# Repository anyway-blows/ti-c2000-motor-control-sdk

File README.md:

# ti-c2000-motor-control-sdk
ti-c2000-motor-control-sdk

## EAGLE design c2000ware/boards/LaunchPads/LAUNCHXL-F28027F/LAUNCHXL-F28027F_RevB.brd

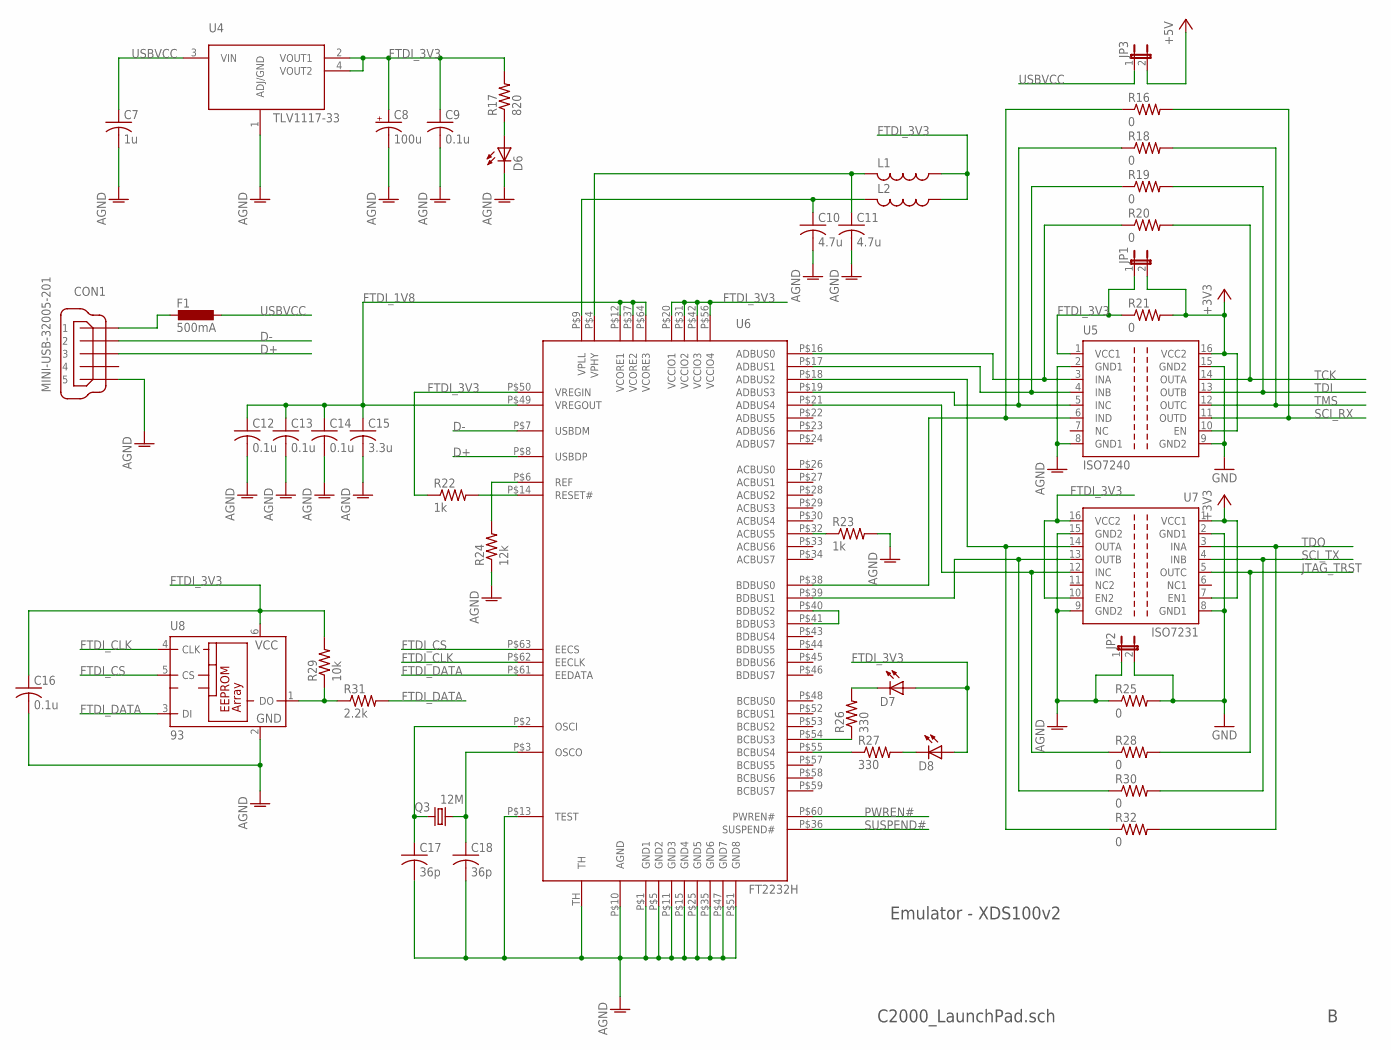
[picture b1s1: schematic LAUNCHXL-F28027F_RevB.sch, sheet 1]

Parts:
C7: 1u; C0402
C8: 100u; B/3528-21R
C9, C12, C13, C14, C16: 0.1u; C0402
C10, C11: 4.7u; C0402
C15: 3.3u; C0402
C17, C18: 36p; C0402
CON1: MINI-USB-32005-201; 32005-201
D6, D7, D8: LEDCHIP-LED0603; CHIP-LED0603
F1: 500mA; L1812
JP1, JP2, JP3: JP1ENORM; JP1
L1, L2: L-US0402; R0402
Q3: 12M; HC49UP
R16, R18, R19, R20, R21, R25, R28, R30, R32: 0; R1206
R17: 820; R0402
R22, R23: 1k; R0402
R24: 12k; R0402
R26, R27: 330; R0402
R29: 10k; R0402
R31: 2.2k; R0402
U4: TLV1117-33; SOT223
U5: ISO7240; SO-16DW
U6: FT2232H; QFN64
U7: ISO7231; SO-16DW
U8: 93; SOT23-6

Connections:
+3V3: JP1.2, R21.2, U5.10 (EN), U5.16 (VCC2), U7.1 (VCC1), U7.7 (EN1); also elsewhere on the board
+5V: JP3.2; also elsewhere on the board
AGND: C7.2, C8.-, C9.2, C10.2, C11.2, C12.2, C13.2, C14.2, C15.2, C16.2, C17.2, C18.2, CON1.5, D6.C, JP2.1, R23.2, R24.1, R25.1, U4.1 (ADJ/GND), U5.2 (GND1), U5.8 (GND1), U6.P$1 (GND1), U6.P$5 (GND2), U6.P$10 (AGND), U6.P$11 (GND3), U6.P$13 (TEST), U6.P$15 (GND4), U6.P$25 (GND5), U6.P$35 (GND6), U6.P$47 (GND7), U6.P$51 (GND8), U6.TH, U7.9 (GND2), U7.15 (GND2), U8.2 (GND)
D+: CON1.3, U6.P$8 (USBDP)
D-: CON1.2, U6.P$7 (USBDM)
FTDI_1V8: C12.1, C13.1, C14.1, C15.1, U6.P$12 (VCORE1), U6.P$37 (VCORE2), U6.P$49 (VREGOUT), U6.P$64 (VCORE3)
FTDI_3V3: C8.+, C9.1, C16.1, D7.A, D8.A, JP1.1, L1.1, L2.1, R17.2, R21.1, R22.1, R29.2, U4.2 (VOUT1), U4.4 (VOUT2), U5.1 (VCC1), U6.P$20 (VCCIO1), U6.P$31 (VCCIO2), U6.P$42 (VCCIO3), U6.P$50 (VREGIN), U6.P$56 (VCCIO4), U7.10 (EN2), U7.16 (VCC2), U8.6 (VCC)
FTDI_CLK: U6.P$62 (EECLK), U8.4 (CLK)
FTDI_CS: U6.P$63 (EECS), U8.5 (CS)
FTDI_DATA: R31.2, U6.P$61 (EEDATA), U8.3 (DI)
GND: JP2.2, R25.2, U5.9 (GND2), U5.15 (GND2), U7.2 (GND1), U7.8 (GND1); also elsewhere on the board
JTAG_TRST: R28.2, U7.5 (OUTC); also elsewhere on the board
unnamed: R20.1, U5.3 (INA), U6.P$16 (ADBUS0)
unnamed: C17.1, Q3.1, U6.P$2 (OSCI)
unnamed: R19.1, U5.4 (INB), U6.P$17 (ADBUS1)
unnamed: R32.1, U6.P$18 (ADBUS2), U7.14 (OUTA)
unnamed: R18.1, U5.5 (INC), U6.P$19 (ADBUS3)
unnamed: C18.1, Q3.2, U6.P$3 (OSCO)
unnamed: R29.1, R31.1, U8.1 (DO)
unnamed: R28.1, U6.P$21 (ADBUS4), U7.12 (INC)
unnamed: R23.1, U6.P$32 (ACBUS5)
unnamed: U6.P$40 (BDBUS2), U6.P$41 (BDBUS3)
unnamed: R16.1, U5.6 (IND), U6.P$38 (BDBUS0)
unnamed: R24.2, U6.P$6 (REF)
unnamed: R26.1, U6.P$54 (BCBUS3)
unnamed: C11.1, L1.2, U6.P$4 (VPHY)
unnamed: R30.1, U6.P$39 (BDBUS1), U7.13 (OUTB)
unnamed: R27.1, U6.P$55 (BCBUS4)
unnamed: D7.C, R26.2
unnamed: D8.C, R27.2
unnamed: C10.1, L2.2, U6.P$9 (VPLL)
unnamed: D6.A, R17.1
unnamed: R22.2, U6.P$14 (RESET#)
PWREN#: U6.P$60 (PWREN#)
SCI_RX: R16.2, U5.11 (OUTD); also elsewhere on the board
SCI_TX: R30.2, U7.4 (INB); also elsewhere on the board
SUSPEND#: U6.P$36 (SUSPEND#)
TCK: R20.2, U5.14 (OUTA); also elsewhere on the board
TDI: R19.2, U5.13 (OUTB); also elsewhere on the board
TDO: R32.2, U7.3 (INA); also elsewhere on the board
TMS: R18.2, U5.12 (OUTC); also elsewhere on the board
USBVCC: C7.1, F1.1, JP3.1, U4.3 (VIN)
XUSB: CON1.1, F1.2

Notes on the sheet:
Emulator - XDS100v2
C2000_LaunchPad.sch

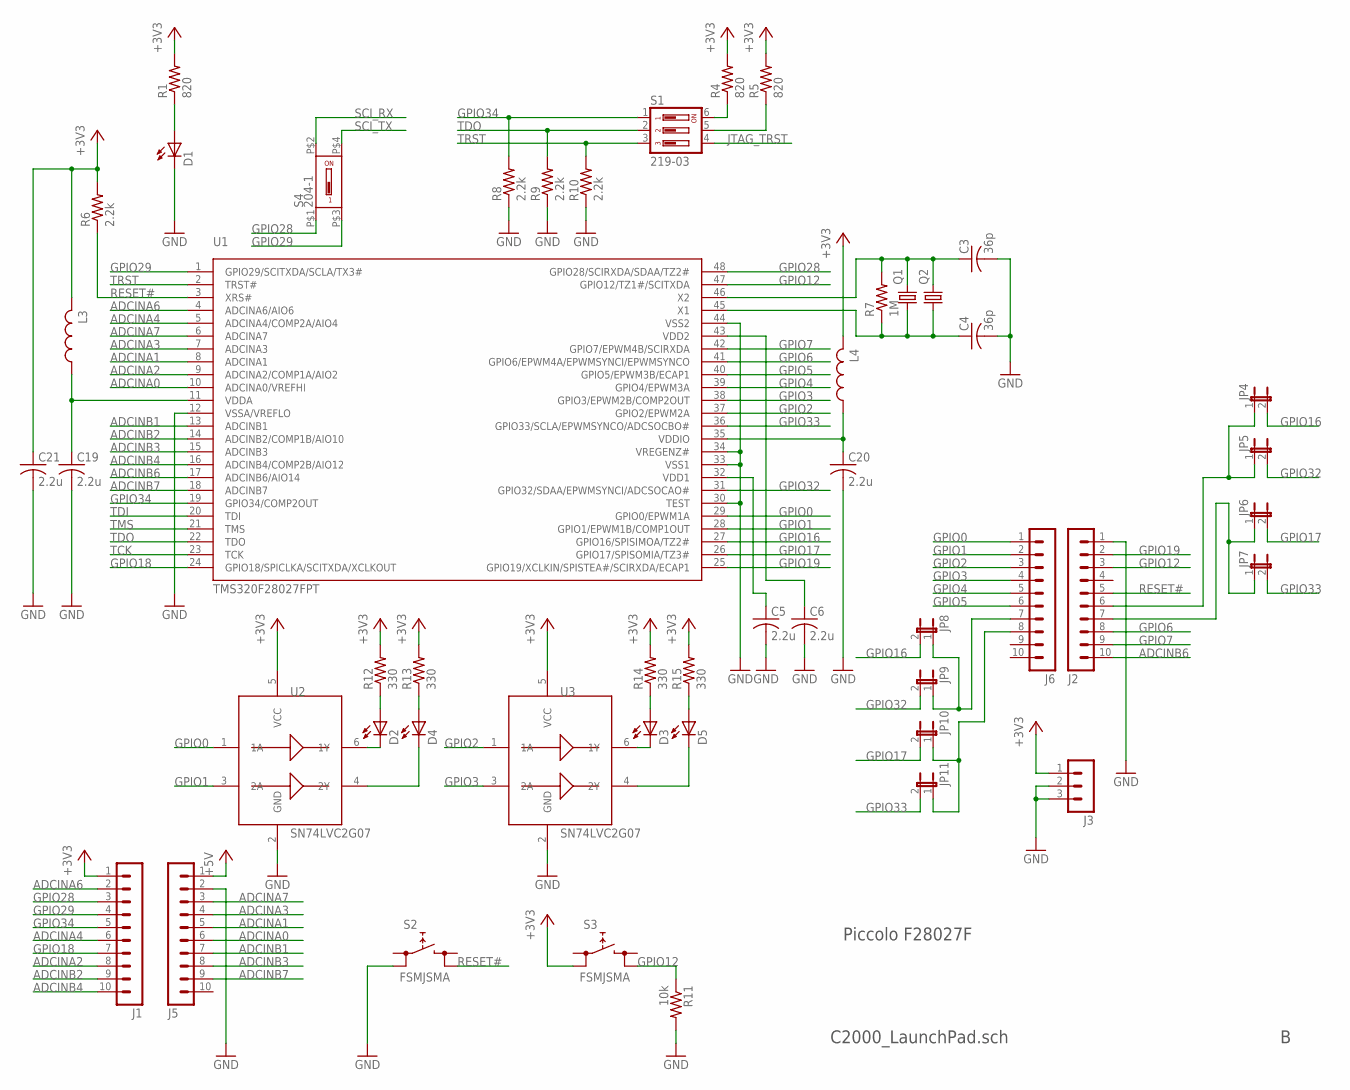
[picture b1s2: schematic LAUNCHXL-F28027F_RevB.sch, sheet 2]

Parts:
C3, C4: 36p; C0402
C5, C6, C19, C20, C21: 2.2u; C0402
D1, D2, D3, D4, D5: LEDCHIP-LED0603; CHIP-LED0603
J1, J2, J5, J6: MA10-1
J3: MA03-1
JP4, JP5, JP6, JP7, JP8, JP9, JP10, JP11: JP1ECUT; C0402
L3, L4: L-US0402; R0402
Q1: CRYSTALHC49S; HC49/S
Q2: CRYSTALHC49UP; HC49UP
R1, R4, R5: 820; R0402
R6, R8, R9, R10: 2.2k; R0402
R7: 1M; R0402
R11: 10k; R0402
R12, R13, R14, R15: 330; R0402
S1: 219-03; CTS-219-03
S2, S3: FSMJSMA
S4: 204-1; CTS-204-1
U1: TMS320F28027FPT; PQFP48
U2, U3: SN74LVC2G07; SOT23-6-DBV

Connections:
+3V3: C21.1, J1.1, J3.1, L3.2, L4.2, R1.2, R4.2, R5.2, R6.2, R12.2, R13.2, R14.2, R15.2, S3.P$2 (0), U2.5 (VCC), U3.5 (VCC); also elsewhere on the board
+5V: J5.1; also elsewhere on the board
ADCINA0: J5.6, U1.10 (ADCINA0/VREFHI)
ADCINA1: J5.5, U1.8 (ADCINA1)
ADCINA2: J1.8, U1.9 (ADCINA2/COMP1A/AIO2)
ADCINA3: J5.4, U1.7 (ADCINA3)
ADCINA4: J1.6, U1.5 (ADCINA4/COMP2A/AIO4)
ADCINA6: J1.2, U1.4 (ADCINA6/AIO6)
ADCINA7: J5.3, U1.6 (ADCINA7)
ADCINB1: J5.7, U1.13 (ADCINB1)
ADCINB2: J1.9, U1.14 (ADCINB2/COMP1B/AIO10)
ADCINB3: J5.8, U1.15 (ADCINB3)
ADCINB4: J1.10, U1.16 (ADCINB4/COMP2B/AIO12)
ADCINB6: J2.10, U1.17 (ADCINB6/AIO14)
ADCINB7: J5.9, U1.18 (ADCINB7)
GND: C3.2, C4.2, C5.2, C6.2, C19.2, C20.2, C21.2, D1.C, J2.1, J3.2, J3.3, J5.2, R8.1, R9.1, R10.1, R11.2, S2.P$2 (0), U1.12 (VSSA/VREFLO), U1.30 (TEST), U1.33 (VSS1), U1.34 (VREGENZ#), U1.44 (VSS2), U2.2 (GND), U3.2 (GND); also elsewhere on the board
GPIO0: J6.1, U1.29 (GPIO0/EPWM1A), U2.1 (1A)
GPIO1: J6.2, U1.28 (GPIO1/EPWM1B/COMP1OUT), U2.3 (2A)
GPIO2: J6.3, U1.37 (GPIO2/EPWM2A), U3.1 (1A)
GPIO3: J6.4, U1.38 (GPIO3/EPWM2B/COMP2OUT), U3.3 (2A)
GPIO4: J6.5, U1.39 (GPIO4/EPWM3A)
GPIO5: J6.6, U1.40 (GPIO5/EPWM3B/ECAP1)
GPIO6: J2.8, U1.41 (GPIO6/EPWM4A/EPWMSYNCI/EPWMSYNCO)
GPIO7: J2.9, U1.42 (GPIO7/EPWM4B/SCIRXDA)
GPIO12: J2.3, R11.1, S3.P$4 (1), U1.47 (GPIO12/TZ1#/SCITXDA)
GPIO16: JP4.2, JP8.2, U1.27 (GPIO16/SPISIMOA/TZ2#)
GPIO17: JP6.2, JP10.2, U1.26 (GPIO17/SPISOMIA/TZ3#)
GPIO18: J1.7, U1.24 (GPIO18/SPICLKA/SCITXDA/XCLKOUT)
GPIO19: J2.2, U1.25 (GPIO19/XCLKIN/SPISTEA#/SCIRXDA/ECAP1)
GPIO28: J1.3, S4.P$1 (1), U1.48 (GPIO28/SCIRXDA/SDAA/TZ2#)
GPIO29: J1.4, S4.P$3 (3), U1.1 (GPIO29/SCITXDA/SCLA/TX3#)
GPIO32: JP5.2, JP9.2, U1.31 (GPIO32/SDAA/EPWMSYNCI/ADCSOCAO#)
GPIO33: JP7.2, JP11.2, U1.36 (GPIO33/SCLA/EPWMSYNCO/ADCSOCBO#)
GPIO34: J1.5, R8.2, S1.1, U1.19 (GPIO34/COMP2OUT)
J2: J2.6, JP4.1, JP5.1
JTAG_TRST: S1.4; also elsewhere on the board
unnamed: C19.1, L3.1, U1.11 (VDDA)
unnamed: C3.1, Q1.2, Q2.2, R7.2, U1.46 (X2)
unnamed: R4.1, S1.6
unnamed: R5.1, S1.5
unnamed: C4.1, Q1.1, Q2.1, R7.1, U1.45 (X1)
unnamed: C5.1, U1.32 (VDD1)
unnamed: C6.1, U1.43 (VDD2)
unnamed: D1.A, R1.1
unnamed: D2.C, U2.6 (1Y)
unnamed: D4.C, U2.4 (2Y)
unnamed: D2.A, R12.1
unnamed: D4.A, R13.1
unnamed: D3.C, U3.6 (1Y)
unnamed: D5.C, U3.4 (2Y)
unnamed: D3.A, R14.1
unnamed: D5.A, R15.1
unnamed: C20.1, L4.1, U1.35 (VDDIO)
unnamed: J6.7, JP8.1, JP9.1
unnamed: J2.7, JP6.1, JP7.1
unnamed: J6.8, JP10.1, JP11.1
RESET#: J2.5, R6.1, S2.P$4 (1), U1.3 (XRS#)
SCI_RX: S4.P$2 (2); also elsewhere on the board
SCI_TX: S4.P$4 (4); also elsewhere on the board
TCK: U1.23 (TCK); also elsewhere on the board
TDI: U1.20 (TDI); also elsewhere on the board
TDO: R9.2, S1.2, U1.22 (TDO); also elsewhere on the board
TMS: U1.21 (TMS); also elsewhere on the board
TRST: R10.2, S1.3, U1.2 (TRST#)

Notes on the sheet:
Piccolo F28027F
C2000_LaunchPad.sch

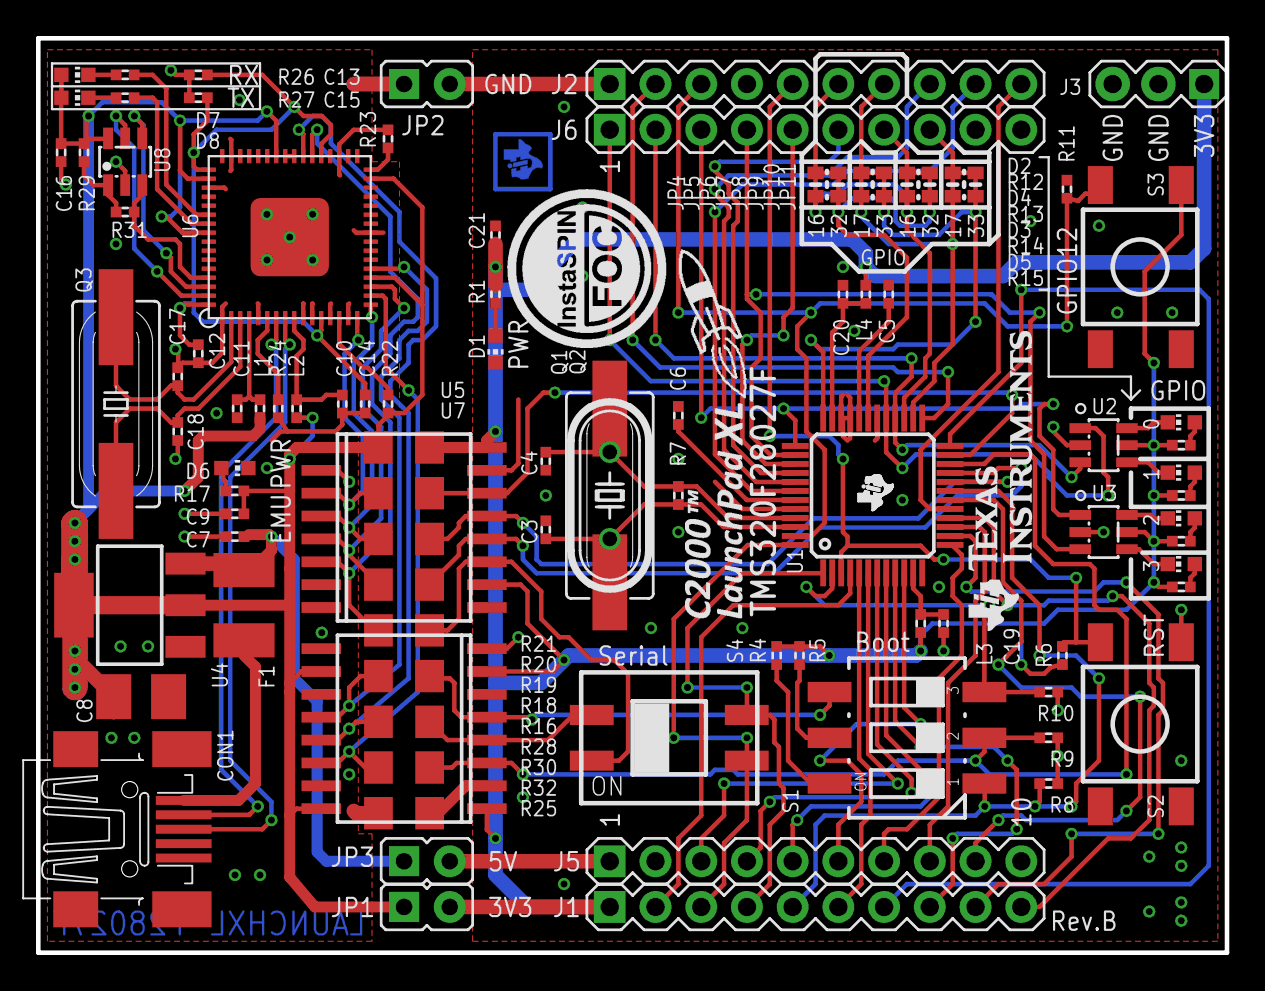
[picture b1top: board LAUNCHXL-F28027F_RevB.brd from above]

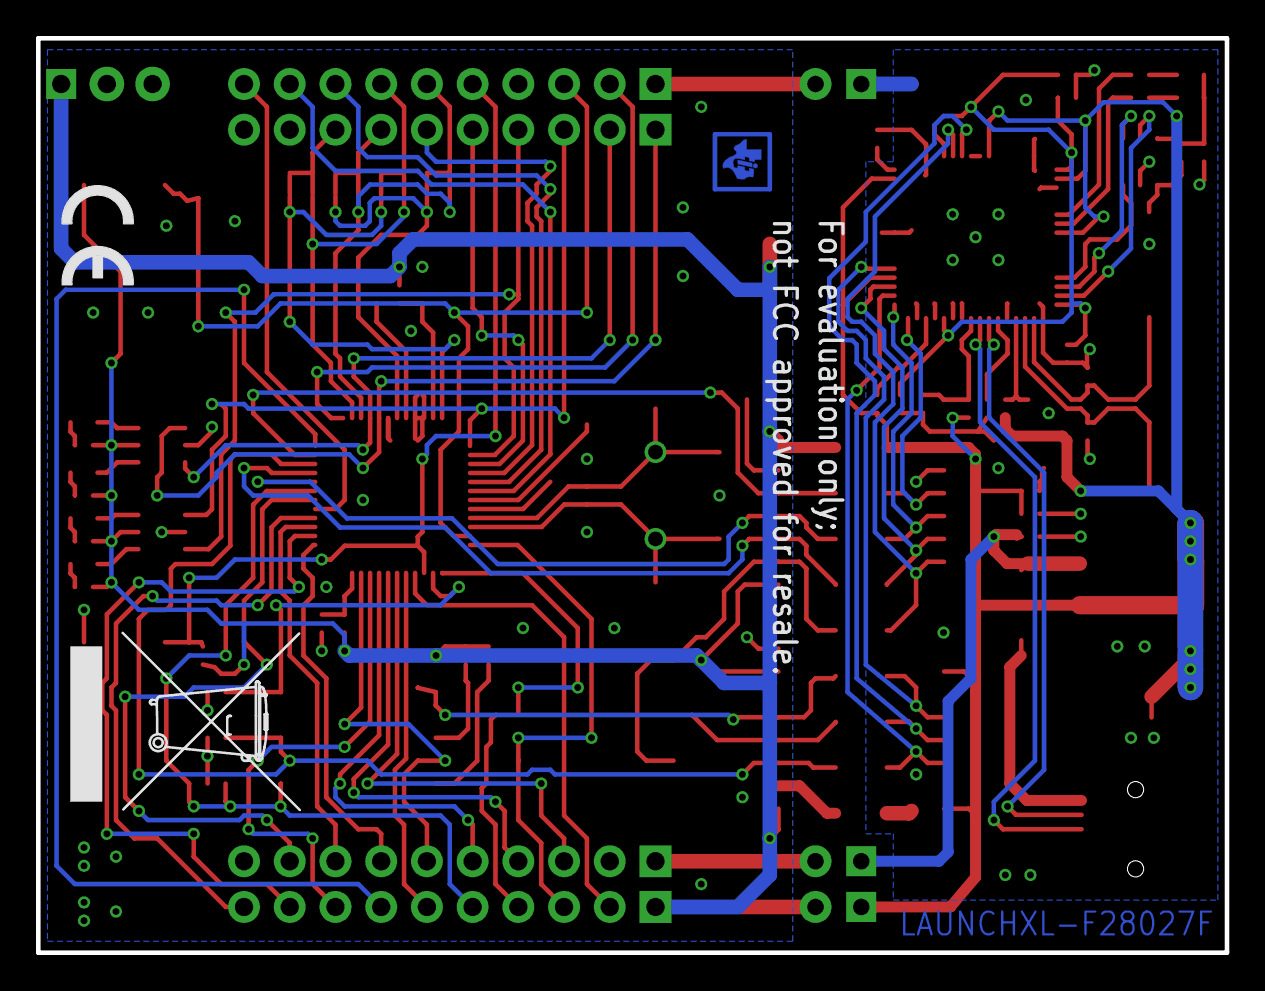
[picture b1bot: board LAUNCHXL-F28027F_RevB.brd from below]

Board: 2 copper layers, 66.0 x 50.8 mm, 103 parts (4 on the bottom side), 95 nets.

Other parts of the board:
U$1: TRADEMARK
U$2: XL
U$3: MSP430_LAB_TILOGO_SMALL
U$4: STI_LOGO_LOGO16_TPLACE
U$5: STI_LOGO_ROCKET
U$6: STI_LOGO_LAUNCHPADC2K
U$7: CE-4MM
U$8: MSP430_LAB_TILOGO_SMALL_TSTOP
U$11: TONNE_10.00

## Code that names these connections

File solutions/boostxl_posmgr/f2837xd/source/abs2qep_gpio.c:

//#############################################################################
//
// FILE:           abs2qep_gpio.c
//
// Description:    Example project for using pto_abs2qep Library.
//
//#############################################################################
// $TI Release: MotorControl SDK v3.03.00.00 $
// $Release Date: Tue Sep 21 16:33:28 CDT 2021 $
// $Copyright:
// Copyright (C) 2017-2021 Texas Instruments Incorporated - http://www.ti.com/
//
// Redistribution and use in source and binary forms, with or without
// modification, are permitted provided that the following conditions
// are met:
// 
//   Redistributions of source code must retain the above copyright
//   notice, this list of conditions and the following disclaimer.
// 
//   Redistributions in binary form must reproduce the above copyright
//   notice, this list of conditions and the following disclaimer in the
//   documentation and/or other materials provided with the
//   distribution.
// 
//   Neither the name of Texas Instruments Incorporated nor the names of
//   its contributors may be used to endorse or promote products derived
//   from this software without specific prior written permission.
// 
// THIS SOFTWARE IS PROVIDED BY THE COPYRIGHT HOLDERS AND CONTRIBUTORS
// "AS IS" AND ANY EXPRESS OR IMPLIED WARRANTIES, INCLUDING, BUT NOT
// LIMITED TO, THE IMPLIED WARRANTIES OF MERCHANTABILITY AND FITNESS FOR
// A PARTICULAR PURPOSE ARE DISCLAIMED. IN NO EVENT SHALL THE COPYRIGHT
// OWNER OR CONTRIBUTORS BE LIABLE FOR ANY DIRECT, INDIRECT, INCIDENTAL,
// SPECIAL, EXEMPLARY, OR CONSEQUENTIAL DAMAGES (INCLUDING, BUT NOT
// LIMITED TO, PROCUREMENT OF SUBSTITUTE GOODS OR SERVICES; LOSS OF USE,
// DATA, OR PROFITS; OR BUSINESS INTERRUPTION) HOWEVER CAUSED AND ON ANY
// THEORY OF LIABILITY, WHETHER IN CONTRACT, STRICT LIABILITY, OR TORT
// (INCLUDING NEGLIGENCE OR OTHERWISE) ARISING IN ANY WAY OUT OF THE USE
// OF THIS SOFTWARE, EVEN IF ADVISED OF THE POSSIBILITY OF SUCH DAMAGE.
// $
//#############################################################################
//
// Included Files
//
#include <stdlib.h>
#include <time.h>
#include "abs2qep.h"
#include "device.h"
#include "driverlib.h"

//
// Configure GPIOs to monitor signals
// Specific to the F2837xd Example
//
void
pto_setupGPIO(void)
{
    //
    // PTO-QEP-A comes out on GPIO16 via OUTPUTXBAR7
    //
    GPIO_setPinConfig(GPIO_16_OUTPUTXBAR7);
    GPIO_setDirectionMode(16, GPIO_DIR_MODE_OUT);
    GPIO_setPadConfig(16, GPIO_PIN_TYPE_STD);

    //
    // PTO-QEP-B comes out on GPIO3 via OUTPUTXBAR2
    //
    GPIO_setPinConfig(GPIO_3_OUTPUTXBAR2);
    GPIO_setDirectionMode(3, GPIO_DIR_MODE_OUT);
    GPIO_setPadConfig(3, GPIO_PIN_TYPE_STD);

    //
    // PTO-QEP-I
    // Configure GPIO1 as EPWM1-B
    // Enable CLB Tile1 OUT2 to replace EPWM1B output
    //
    GPIO_setPinConfig(GPIO_1_EPWM1B);
    GPIO_setDirectionMode(1, GPIO_DIR_MODE_OUT);
    GPIO_setPadConfig(1, GPIO_PIN_TYPE_STD);
    CLB_setOutputMask(CLB1_BASE, CLB_OUTPUT_02, true);

    //
    // RUN/HALT - Test Pin
    // View the state of the RUN/HALT signal in Abs2Qep.
    // Configure GPIO0 as EPWM1A
    // Enable CLB Tile 1 OUT0 to replace EPWM1A
    //
    GPIO_setPinConfig(GPIO_0_EPWM1A);
    GPIO_setDirectionMode(0, GPIO_DIR_MODE_OUT);
    GPIO_setPadConfig(0, GPIO_PIN_TYPE_STD);
    CLB_setOutputMask(CLB1_BASE, CLB_OUTPUT_00, true);

    //
    // Configure GPIO32 - Test Pin
    // Toggles when entering the ePWM ISR as
    // a waveform visual marker
    // Remains high if the direction is forward
    // Remains low if the direction is reverse
    //
    GPIO_setPinConfig(GPIO_32_GPIO32);
    GPIO_setDirectionMode(32, GPIO_DIR_MODE_OUT);
    GPIO_setPadConfig(32, GPIO_PIN_TYPE_STD);
    GPIO_writePin(32, 0);

    //
    // Configure the eQEP module pins for
    // monitoring and testing the Abs2Qep
    // output
    //
    GPIO_setPinConfig(GPIO_20_EQEP1A);
    GPIO_setPadConfig(20, GPIO_PIN_TYPE_STD);
    GPIO_setQualificationMode(20, GPIO_QUAL_SYNC);

    GPIO_setPinConfig(GPIO_21_EQEP1B);
    GPIO_setPadConfig(21, GPIO_PIN_TYPE_STD);
    GPIO_setQualificationMode(21, GPIO_QUAL_SYNC);

    GPIO_setPinConfig(GPIO_99_EQEP1I);
    GPIO_setPadConfig(99, GPIO_PIN_TYPE_STD);
    GPIO_setQualificationMode(99, GPIO_QUAL_SYNC);
}
//
// End of File
//

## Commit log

2021-10-27 add: add C2000_Ware_MotorControl_SDK_3.0.3
